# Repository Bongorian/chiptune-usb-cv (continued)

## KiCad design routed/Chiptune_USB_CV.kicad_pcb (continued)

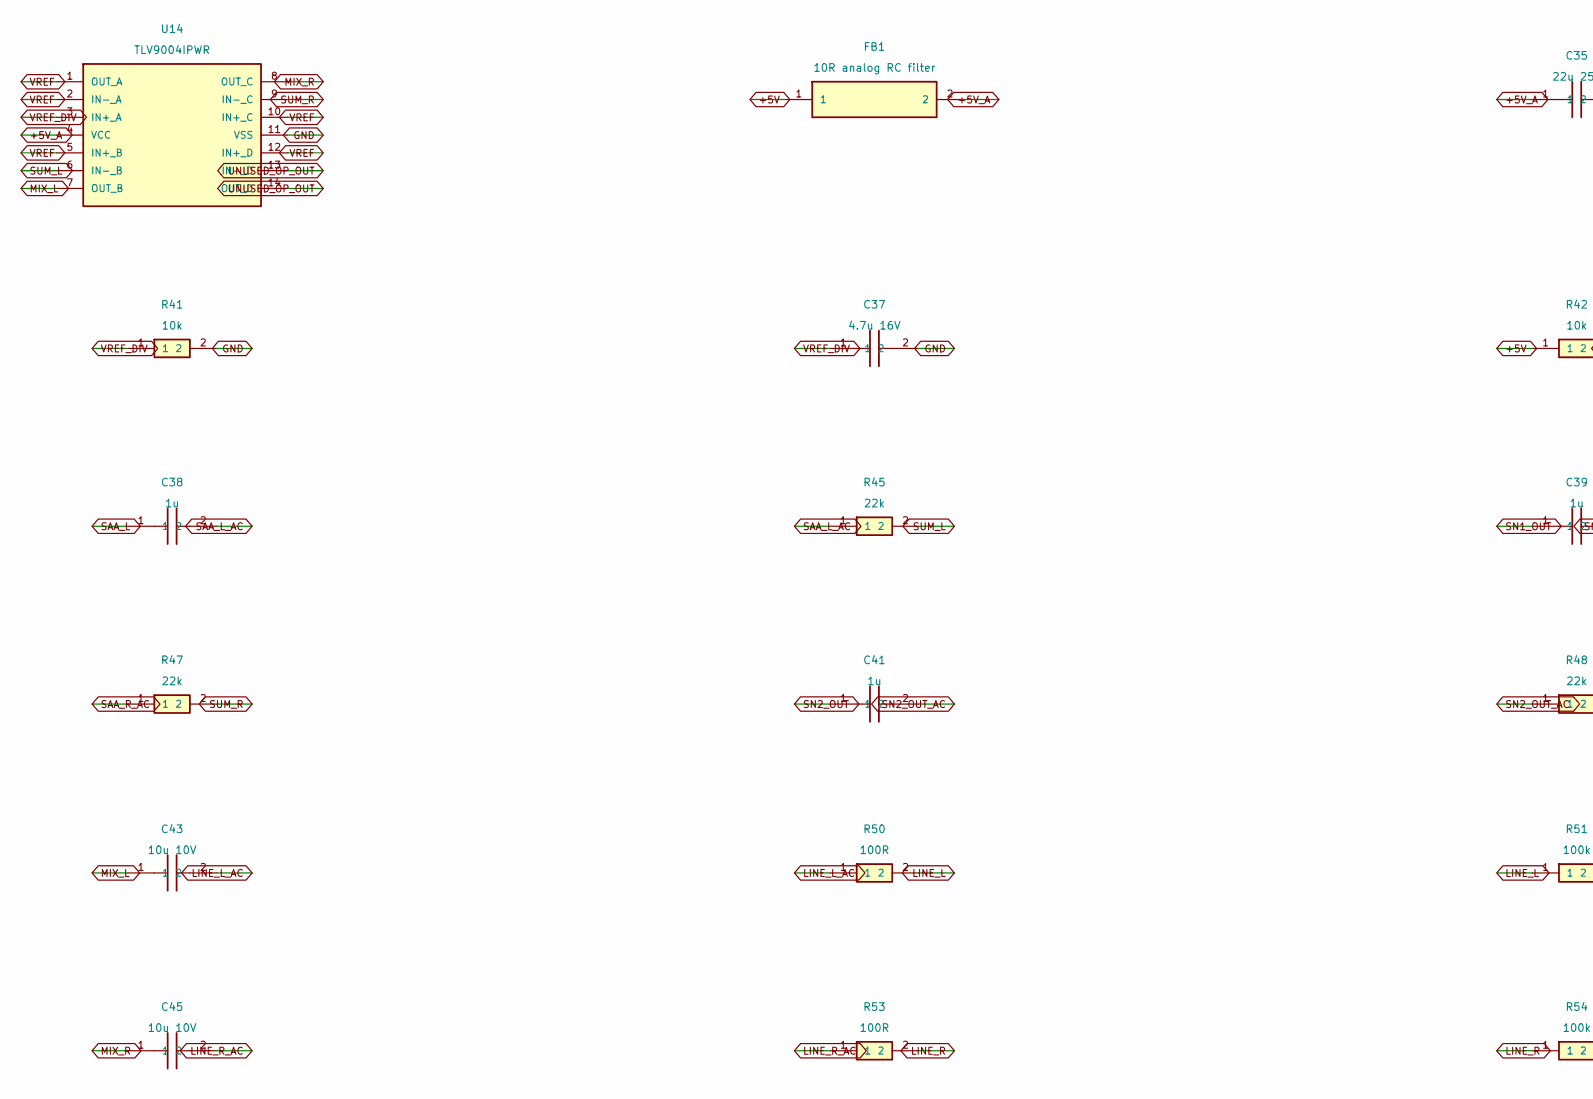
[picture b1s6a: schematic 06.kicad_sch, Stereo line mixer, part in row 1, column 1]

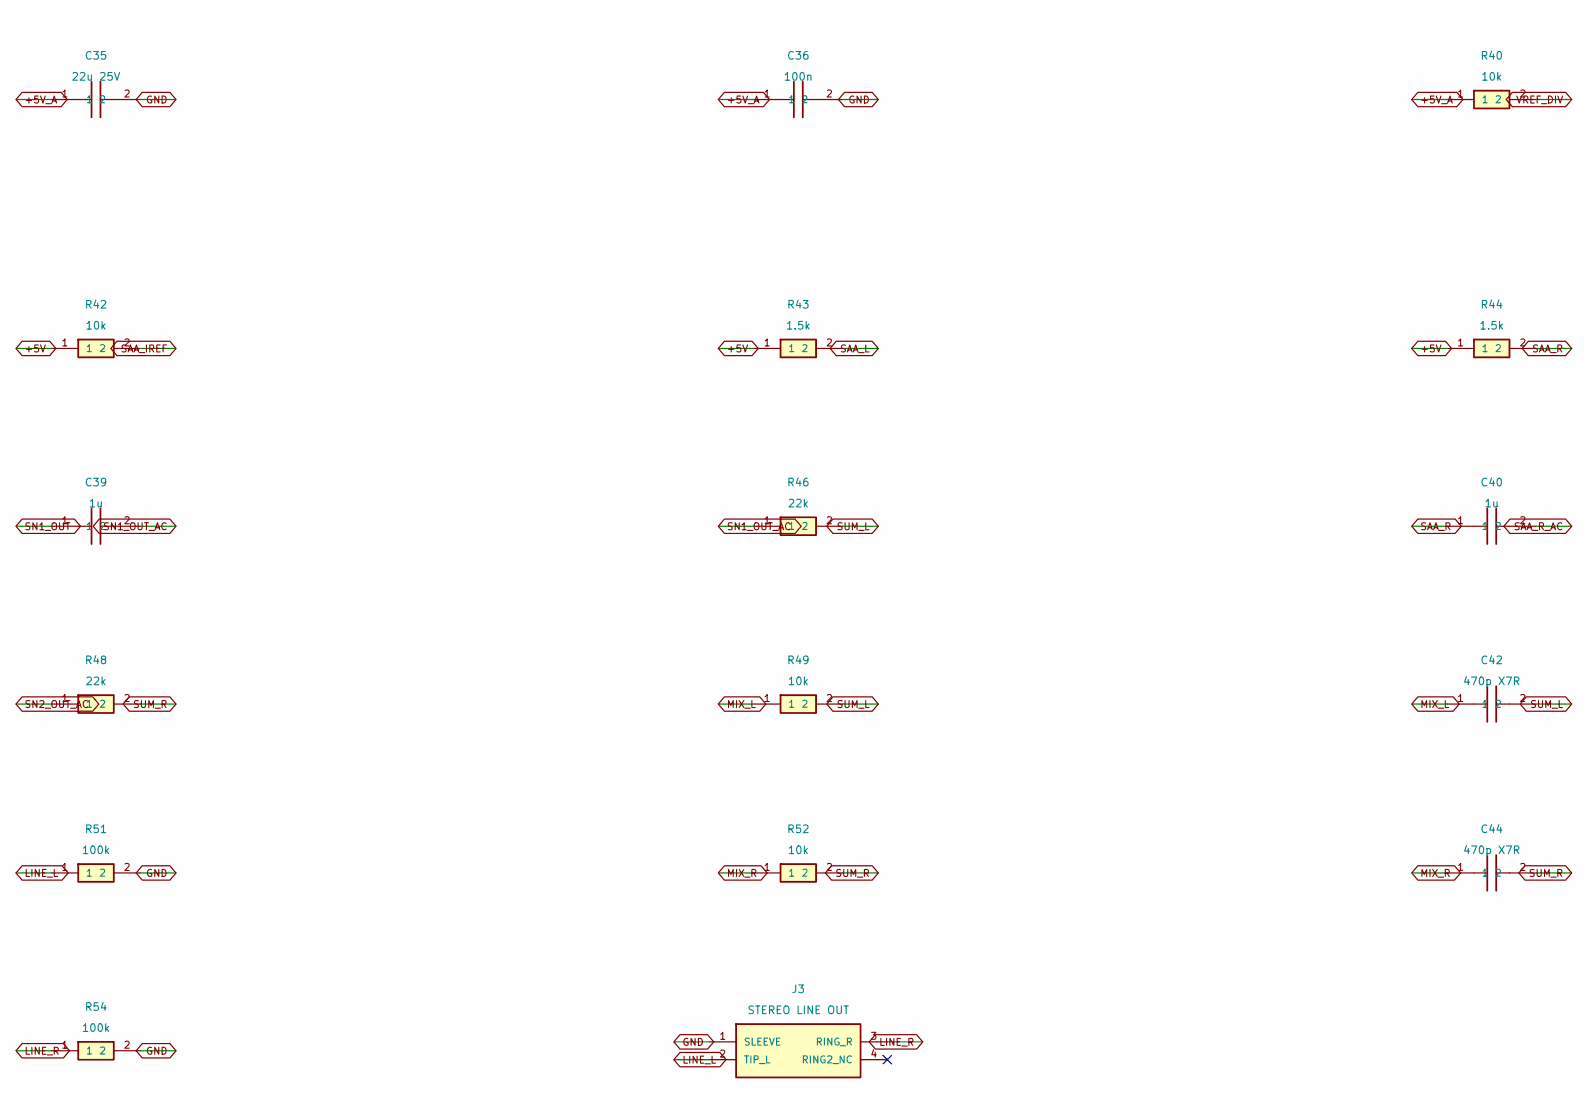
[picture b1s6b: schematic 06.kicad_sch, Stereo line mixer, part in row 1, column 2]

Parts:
C35: 22u 25V; Board_C35; LCSC C45783
C36: 100n; Board_C36; LCSC C14663
C37: 4.7u 16V; Board_C37; LCSC C19666
C38: 1u; Board_C38; LCSC C15849
C39: 1u; Board_C39; LCSC C15849
C40: 1u; Board_C40; LCSC C15849
C41: 1u; Board_C41; LCSC C15849
C42: 470p X7R; Board_C42; LCSC C1620
C43: 10u 10V; Board_C43; LCSC C19702
C44: 470p X7R; Board_C44; LCSC C1620
C45: 10u 10V; Board_C45; LCSC C19702
FB1: 10R analog RC filter; Board_FB1; LCSC C22859
J3: STEREO LINE OUT; Board_J3; LCSC C95562
R40: 10k; Board_R40; LCSC C25804
R41: 10k; Board_R41; LCSC C25804
R42: 10k; Board_R42; LCSC C25804
R43: 1.5k; Board_R43; LCSC C22843
R44: 1.5k; Board_R44; LCSC C22843
R45: 22k; Board_R45; LCSC C31850
R46: 22k; Board_R46; LCSC C31850
R47: 22k; Board_R47; LCSC C31850
R48: 22k; Board_R48; LCSC C31850
R49: 10k; Board_R49; LCSC C25804
R50: 100R; Board_R50; LCSC C22775
R51: 100k; Board_R51; LCSC C25803
R52: 10k; Board_R52; LCSC C25804
R53: 100R; Board_R53; LCSC C22775
R54: 100k; Board_R54; LCSC C25803
U14: TLV9004IPWR; Board_U14; LCSC C2058050

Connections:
+5V: FB1.1, R42.1, R43.1, R44.1; also elsewhere on the board
+5V_A: C35.1, C36.1, FB1.2, R40.1, U14.4 (VCC)
GND: C35.2, C36.2, C37.2, J3.1 (SLEEVE), R41.2, R51.2, R54.2, U14.11 (VSS); also elsewhere on the board
LINE_L: J3.2 (TIP_L), R50.2, R51.1
LINE_L_AC: C43.2, R50.1
LINE_R: J3.3 (RING_R), R53.2, R54.1
LINE_R_AC: C45.2, R53.1
MIX_L: C42.1, C43.1, R49.1, U14.7 (OUT_B)
MIX_R: C44.1, C45.1, R52.1, U14.8 (OUT_C)
SAA_IREF: R42.2; also elsewhere on the board
SAA_L: C38.1, R43.2; also elsewhere on the board
SAA_L_AC: C38.2, R45.1
SAA_R: C40.1, R44.2; also elsewhere on the board
SAA_R_AC: C40.2, R47.1
SN1_OUT: C39.1; also elsewhere on the board
SN1_OUT_AC: C39.2, R46.1
SN2_OUT: C41.1; also elsewhere on the board
SN2_OUT_AC: C41.2, R48.1
SUM_L: C42.2, R45.2, R46.2, R49.2, U14.6 (IN-_B)
SUM_R: C44.2, R47.2, R48.2, R52.2, U14.9 (IN-_C)
UNUSED_OP_OUT: U14.13 (IN-_D), U14.14 (OUT_D)
VREF: U14.1 (OUT_A), U14.2 (IN-_A), U14.5 (IN+_B), U14.10 (IN+_C), U14.12 (IN+_D)
VREF_DIV: C37.1, R40.2, R41.1, U14.3 (IN+_A)

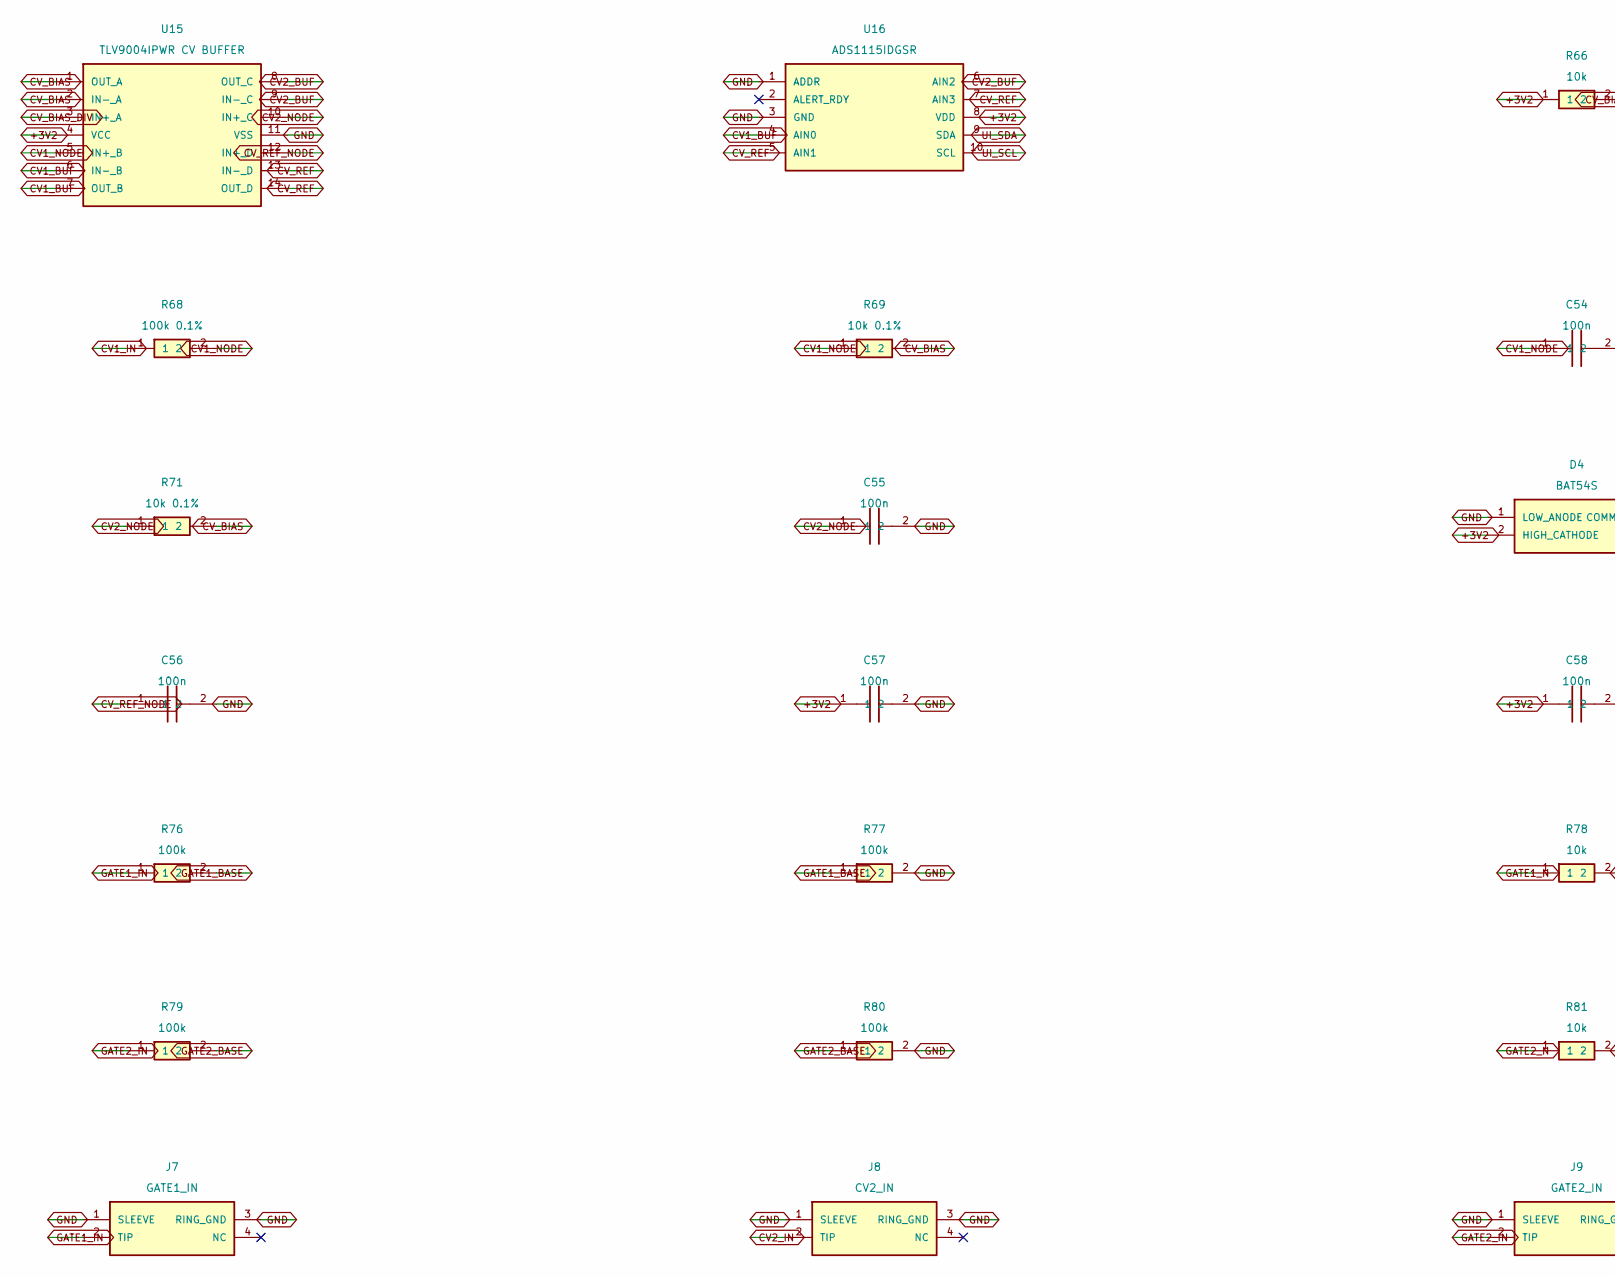
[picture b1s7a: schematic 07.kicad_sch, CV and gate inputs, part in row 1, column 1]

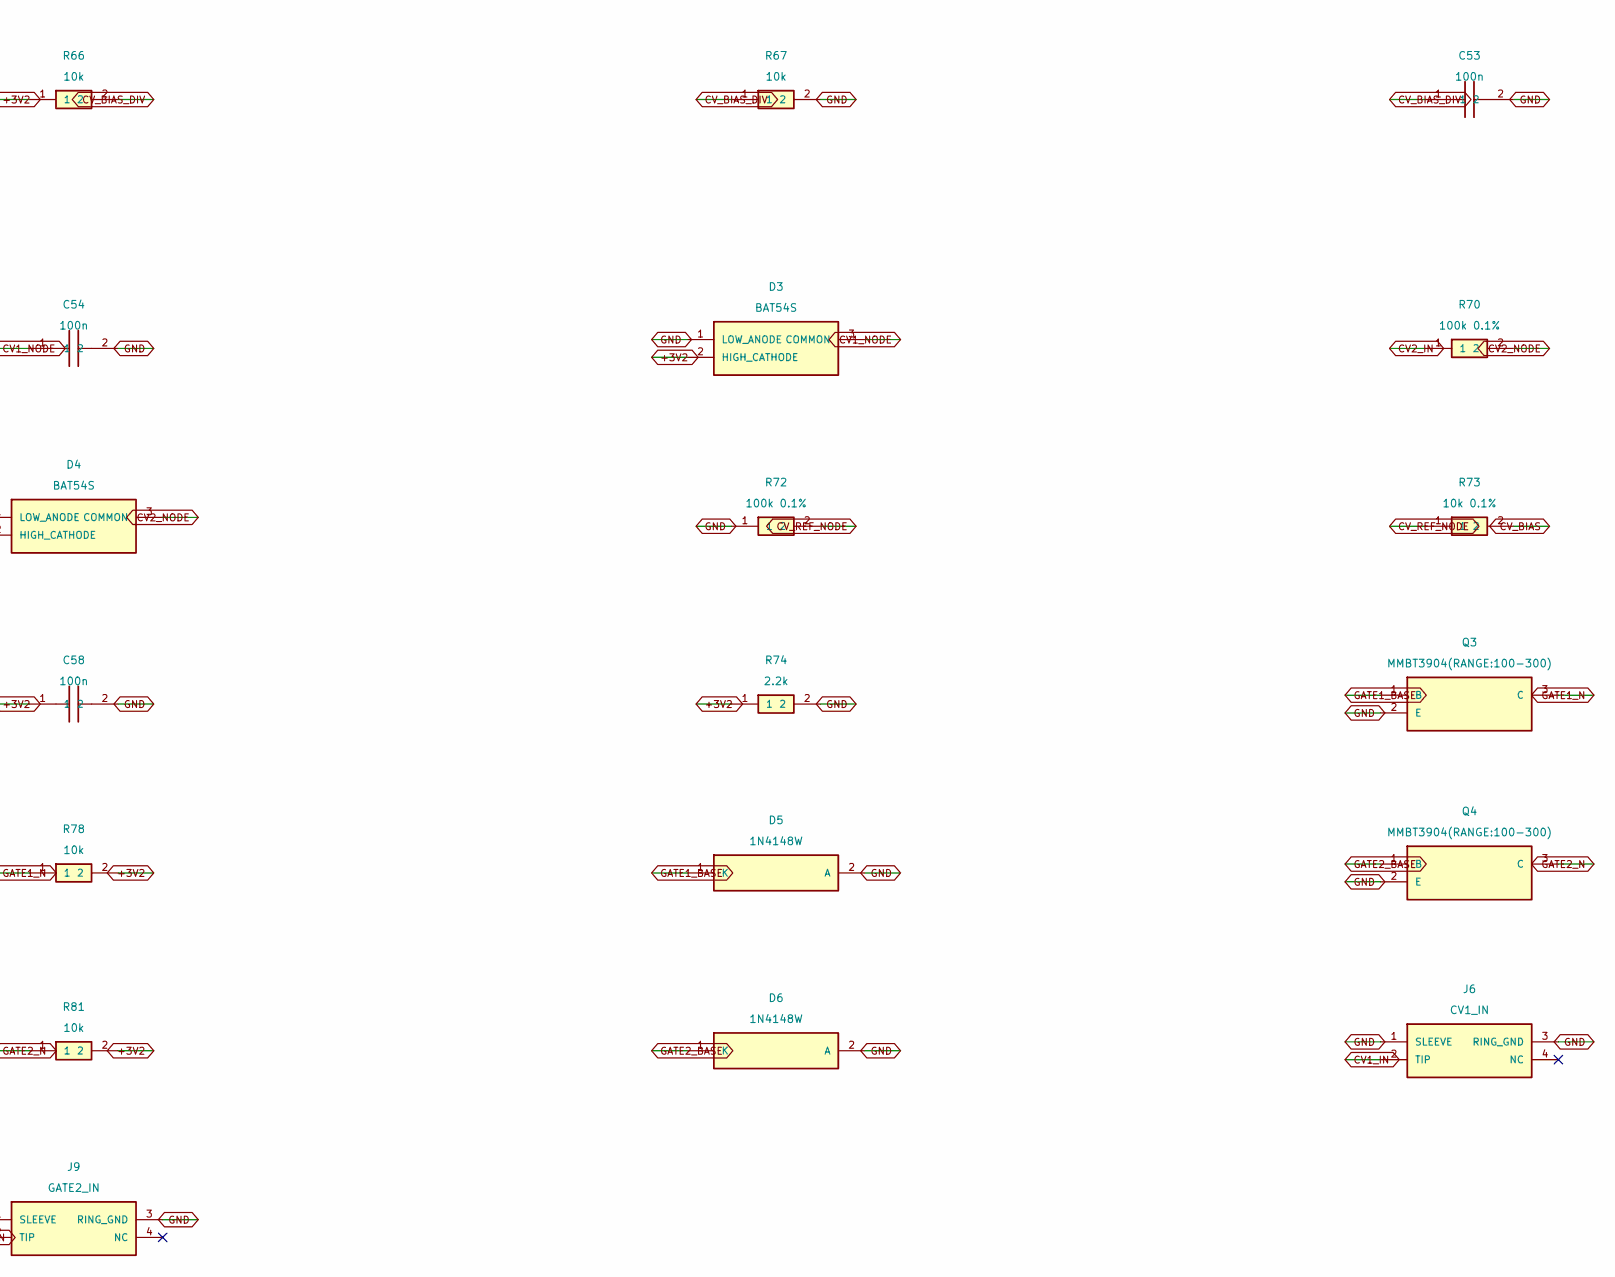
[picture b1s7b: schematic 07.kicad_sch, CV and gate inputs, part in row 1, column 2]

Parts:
C53: 100n; Board_C53; LCSC C14663
C54: 100n; Board_C54; LCSC C14663
C55: 100n; Board_C55; LCSC C14663
C56: 100n; Board_C56; LCSC C14663
C57: 100n; Board_C57; LCSC C14663
C58: 100n; Board_C58; LCSC C14663
D3: BAT54S; Board_D3; LCSC C83935
D4: BAT54S; Board_D4; LCSC C83935
D5: 1N4148W; Board_D5; LCSC C81598
D6: 1N4148W; Board_D6; LCSC C81598
J6: CV1_IN; Board_J6; LCSC C95562
J7: GATE1_IN; Board_J7; LCSC C95562
J8: CV2_IN; Board_J8; LCSC C95562
J9: GATE2_IN; Board_J9; LCSC C95562
Q3: MMBT3904(RANGE:100-300); Board_Q3; LCSC C20526
Q4: MMBT3904(RANGE:100-300); Board_Q4; LCSC C20526
R66: 10k; Board_R66; LCSC C25804
R67: 10k; Board_R67; LCSC C25804
R68: 100k 0.1%; Board_R68; LCSC C855559
R69: 10k 0.1%; Board_R69; LCSC C95204
R70: 100k 0.1%; Board_R70; LCSC C855559
R71: 10k 0.1%; Board_R71; LCSC C95204
R72: 100k 0.1%; Board_R72; LCSC C855559
R73: 10k 0.1%; Board_R73; LCSC C95204
R74: 2.2k; Board_R74; LCSC C4190
R76: 100k; Board_R76; LCSC C25803
R77: 100k; Board_R77; LCSC C25803
R78: 10k; Board_R78; LCSC C25804
R79: 100k; Board_R79; LCSC C25803
R80: 100k; Board_R80; LCSC C25803
R81: 10k; Board_R81; LCSC C25804
U15: TLV9004IPWR CV BUFFER; Board_U15; LCSC C2058050
U16: ADS1115IDGSR; Board_U16; LCSC C37593

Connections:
+3V2: C57.1, C58.1, D3.2 (HIGH_CATHODE), D4.2 (HIGH_CATHODE), R66.1, R74.1, R78.2, R81.2, U15.4 (VCC), U16.8 (VDD); also elsewhere on the board
CV1_BUF: U15.6 (IN-_B), U15.7 (OUT_B), U16.4 (AIN0)
CV1_IN: J6.2 (TIP), R68.1
CV1_NODE: C54.1, D3.3 (COMMON), R68.2, R69.1, U15.5 (IN+_B)
CV2_BUF: U15.8 (OUT_C), U15.9 (IN-_C), U16.6 (AIN2)
CV2_IN: J8.2 (TIP), R70.1
CV2_NODE: C55.1, D4.3 (COMMON), R70.2, R71.1, U15.10 (IN+_C)
CV_BIAS: R69.2, R71.2, R73.2, U15.1 (OUT_A), U15.2 (IN-_A)
CV_BIAS_DIV: C53.1, R66.2, R67.1, U15.3 (IN+_A)
CV_REF: U15.13 (IN-_D), U15.14 (OUT_D), U16.5 (AIN1), U16.7 (AIN3)
CV_REF_NODE: C56.1, R72.2, R73.1, U15.12 (IN+_D)
GATE1_BASE: D5.1 (K), Q3.1 (B), R76.2, R77.1
GATE1_IN: J7.2 (TIP), R76.1
GATE1_N: Q3.3 (C), R78.1; also elsewhere on the board
GATE2_BASE: D6.1 (K), Q4.1 (B), R79.2, R80.1
GATE2_IN: J9.2 (TIP), R79.1
GATE2_N: Q4.3 (C), R81.1; also elsewhere on the board
GND: C53.2, C54.2, C55.2, C56.2, C57.2, C58.2, D3.1 (LOW_ANODE), D4.1 (LOW_ANODE), D5.2 (A), D6.2 (A), J6.1 (SLEEVE), J6.3 (RING_GND), J7.1 (SLEEVE), J7.3 (RING_GND), J8.1 (SLEEVE), J8.3 (RING_GND), J9.1 (SLEEVE), J9.3 (RING_GND), Q3.2 (E), Q4.2 (E), R67.2, R72.1, R74.2, R77.2, R80.2, U15.11 (VSS), U16.1 (ADDR), U16.3 (GND); also elsewhere on the board
UI_SCL: U16.10 (SCL); also elsewhere on the board
UI_SDA: U16.9 (SDA); also elsewhere on the board

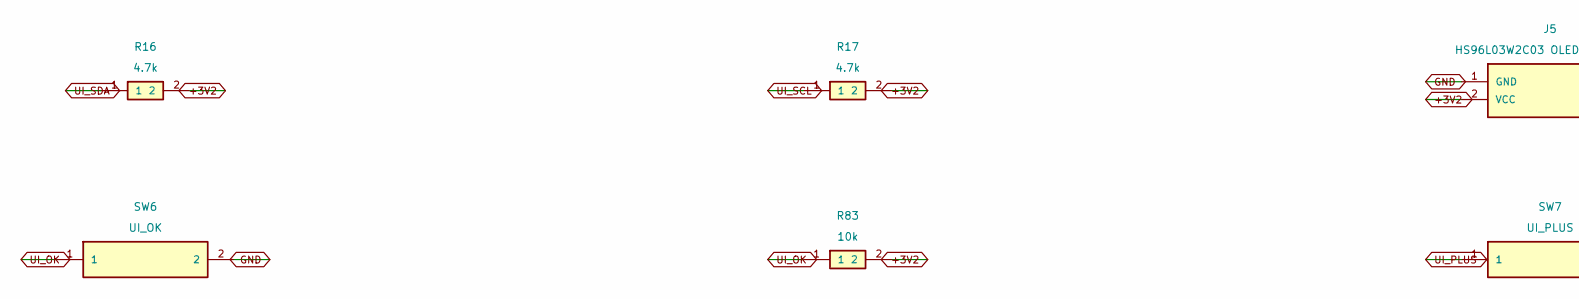
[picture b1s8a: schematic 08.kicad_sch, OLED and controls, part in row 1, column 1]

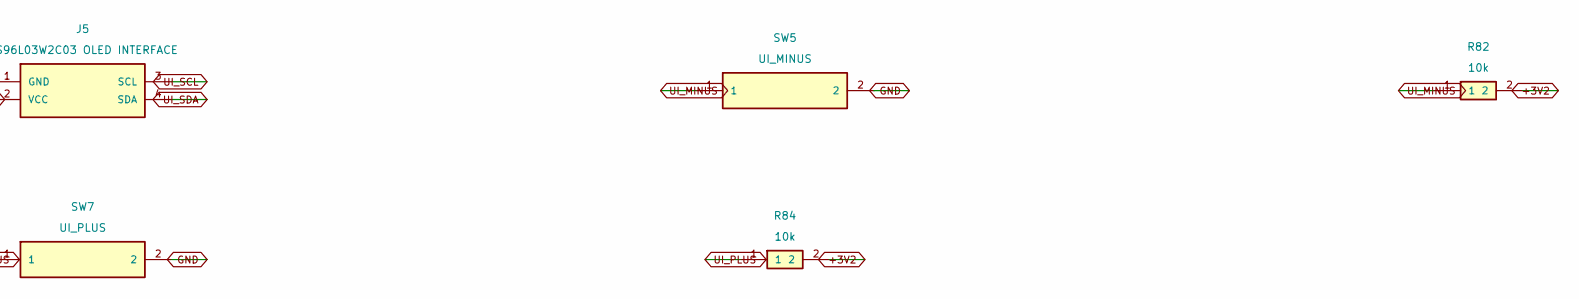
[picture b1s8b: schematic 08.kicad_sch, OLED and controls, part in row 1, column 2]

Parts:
J5: HS96L03W2C03 OLED INTERFACE; Board_J5; LCSC C5248080
R16: 4.7k; Board_R16; LCSC C23162
R17: 4.7k; Board_R17; LCSC C23162
R82: 10k; Board_R82; LCSC C25804
R83: 10k; Board_R83; LCSC C25804
R84: 10k; Board_R84; LCSC C25804
SW5: UI_MINUS; Board_SW5; LCSC C318884
SW6: UI_OK; Board_SW6; LCSC C318884
SW7: UI_PLUS; Board_SW7; LCSC C318884

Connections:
+3V2: J5.2 (VCC), R16.2, R17.2, R82.2, R83.2, R84.2; also elsewhere on the board
GND: J5.1 (GND), SW5.2, SW6.2, SW7.2; also elsewhere on the board
UI_MINUS: R82.1, SW5.1; also elsewhere on the board
UI_OK: R83.1, SW6.1; also elsewhere on the board
UI_PLUS: R84.1, SW7.1; also elsewhere on the board
UI_SCL: J5.3 (SCL), R17.1; also elsewhere on the board
UI_SDA: J5.4 (SDA), R16.1; also elsewhere on the board

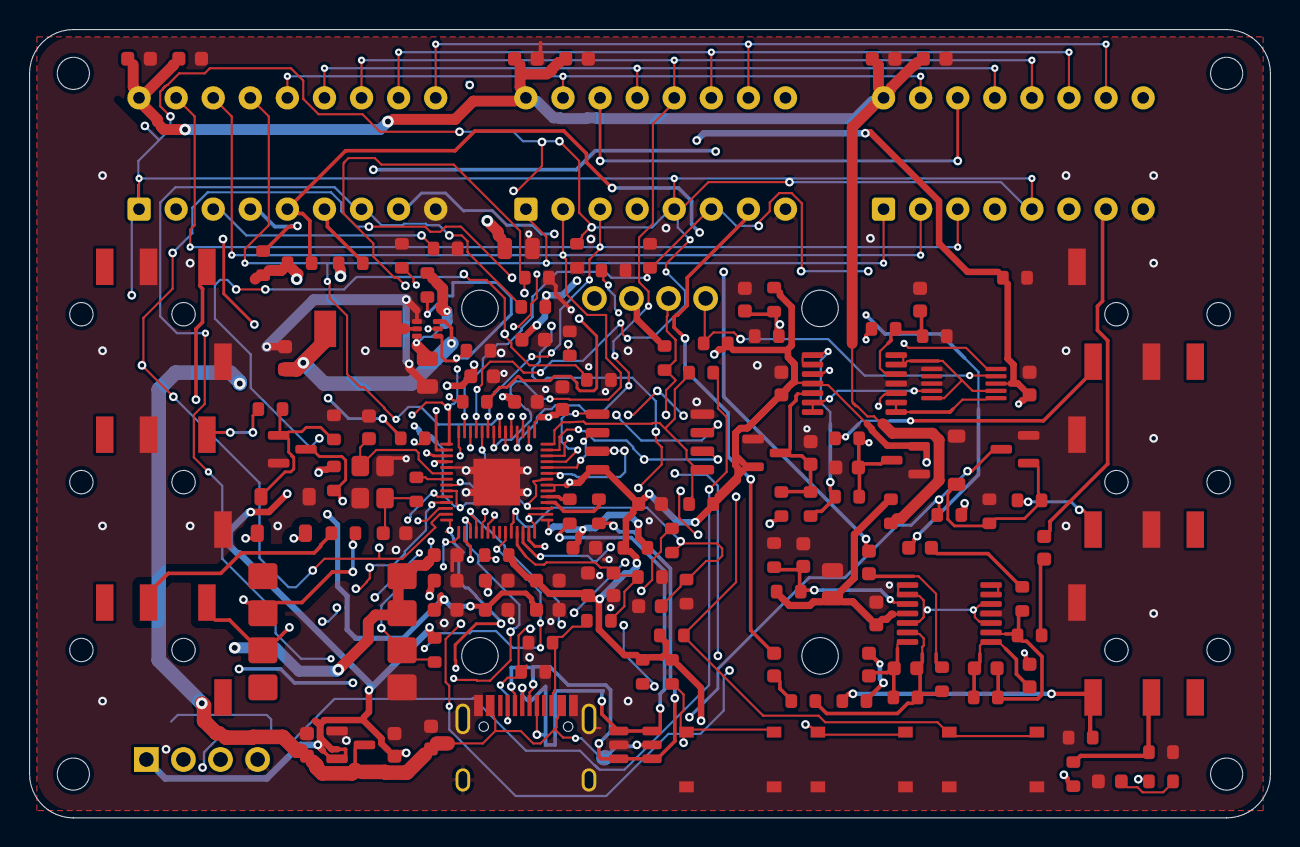
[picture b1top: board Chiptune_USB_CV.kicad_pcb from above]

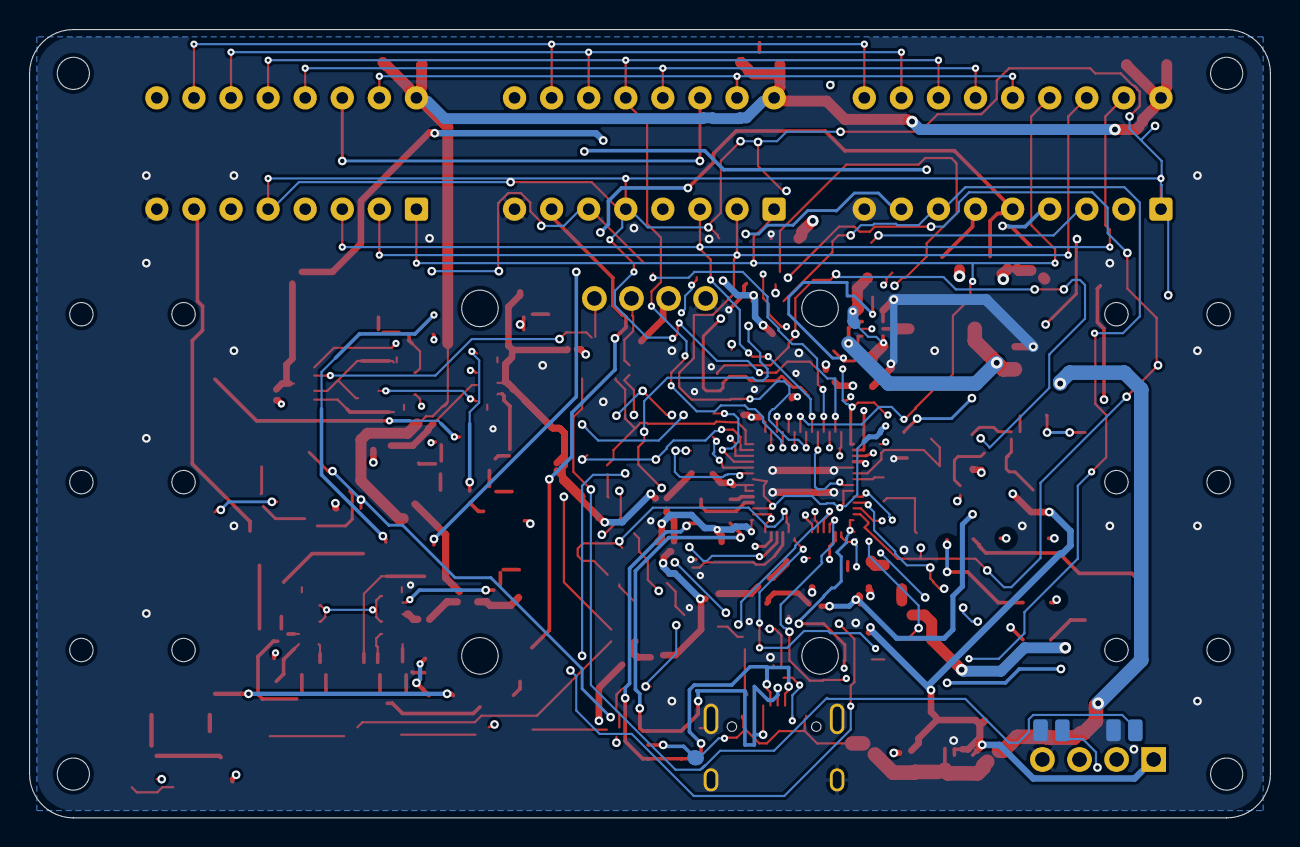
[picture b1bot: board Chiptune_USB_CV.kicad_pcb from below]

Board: 4 copper layers, 85.0 x 54.0 mm, 152 parts (2 on the bottom side), 96 nets.

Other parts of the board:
H1: MountingHole_2.2mm_M2; Board_H1
H2: MountingHole_2.2mm_M2; Board_H2
H3: MountingHole_2.2mm_M2; Board_H3
H4: MountingHole_2.2mm_M2; Board_H4

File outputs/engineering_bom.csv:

Reference,Value,Footprint,LCSC,Side,Notes
U1,RP2040,Chiptune:Board_U1,C2040,F,
U2,W25Q16JVSSIQ,Chiptune:Board_U2,C131025,F,
Y1,ABM8-272-T3 12MHz,Chiptune:Board_Y1,C20625731,F,
R1,1k,Chiptune:Board_R1,C21190,F,
C1,15p C0G,Chiptune:Board_C1,C1644,F,
C2,15p C0G,Chiptune:Board_C2,C1644,F,
R2,10k,Chiptune:Board_R2,C25804,F,
R3,10k,Chiptune:Board_R3,C25804,F,
C3,100n,Chiptune:Board_C3,C14663,F,
C4,100n,Chiptune:Board_C4,C14663,F,
C5,100n,Chiptune:Board_C5,C14663,F,
C6,100n,Chiptune:Board_C6,C14663,F,
C7,100n,Chiptune:Board_C7,C14663,F,
C8,100n,Chiptune:Board_C8,C14663,F,
C9,100n,Chiptune:Board_C9,C14663,F,
C10,100n,Chiptune:Board_C10,C14663,F,
C11,100n,Chiptune:Board_C11,C14663,F,
C12,100n,Chiptune:Board_C12,C14663,F,
C13,100n,Chiptune:Board_C13,C14663,F,
C14,1u,Chiptune:Board_C14,C15849,F,
C15,1u,Chiptune:Board_C15,C15849,F,
R4,10R,Chiptune:Board_R4,C22859,F,
R5,1k,Chiptune:Board_R5,C21190,F,
J4,SWD,Chiptune:Board_J4,,F,"Hand solder, optional"
U3,TPS61023DRLR,Chiptune:Board_U3,C919459,F,
R6,100k,Chiptune:Board_R6,C25803,F,
L1,SLO0520H1R0MTT 1uH,Chiptune:Board_L1,C325980,F,"1uH; Isat 8A typ, Irms 5A typ; manufacturer drawing verified"
C16,1u,Chiptune:Board_C16,C15849,F,
C18,22u 25V,Chiptune:Board_C18,C45783,F,
C19,22u 25V,Chiptune:Board_C19,C45783,F,
R7,22k,Chiptune:Board_R7,C31850,F,
R8,3k,Chiptune:Board_R8,C4211,F,
U5,AP2120N-3.2TRG1,Chiptune:Board_U5,C6500828,F,3.2V +/-2%; OLED maximum 3.3V
C21,4.7u 16V,Chiptune:Board_C21,C19666,F,
C22,4.7u 16V,Chiptune:Board_C22,C19666,F,
J1,USB-C MIDI DEVICE / POWER,Chiptune:Board_J1,C165948,F,
U9,USBLC6-2SC6,Chiptune:Board_U9,C7519,F,
R11,27R,Chiptune:Board_R11,C25190,F,
R12,27R,Chiptune:Board_R12,C25190,F,
R16,4.7k,Chiptune:Board_R16,C23162,F,
R17,4.7k,Chiptune:Board_R17,C23162,F,
U10,SAA1099 DIP18,Chiptune:Board_U10,,F,User supplied IC; hand solder DIP18 socket; GPIO0..7 word equals logical byte; reverse8 only for individual PIN_Dn writes
U11,SN76489AN DIP16,Chiptune:Board_U11,,F,"User supplied IC; hand solder DIP16 socket; READY unused, firmware write wait >=10us at 4MHz"
U12,SN76489AN DIP16,Chiptune:Board_U12,,F,"User supplied IC; hand solder DIP16 socket; READY unused, firmware write wait >=10us at 4MHz"
R26,33R,Chiptune:Board_R26,C23140,F,
R27,33R,Chiptune:Board_R27,C23140,F,
R28,100k,Chiptune:Board_R28,C25803,F,
R29,100k,Chiptune:Board_R29,C25803,F,
R30,100k,Chiptune:Board_R30,C25803,F,
R31,100k,Chiptune:Board_R31,C25803,F,
R32,10k,Chiptune:Board_R32,C25804,F,
R35,100k,Chiptune:Board_R35,C25803,F,
R36,100k,Chiptune:Board_R36,C25803,F,
R37,100k,Chiptune:Board_R37,C25803,F,
C28,100n,Chiptune:Board_C28,C14663,F,
C29,100n,Chiptune:Board_C29,C14663,F,
C30,100n,Chiptune:Board_C30,C14663,F,
C31,4.7u 16V,Chiptune:Board_C31,C19666,F,
C32,4.7u 16V,Chiptune:Board_C32,C19666,F,
C33,4.7u 16V,Chiptune:Board_C33,C19666,F,
J2,TRS MIDI IN TYPE A,Chiptune:Board_J2,C95562,F,
R38,220R,Chiptune:Board_R38,C22962,F,
D1,1N4148W,Chiptune:Board_D1,C81598,F,
U13,6N137S(T1),Chiptune:Board_U13,C191867,F,
R39,2.2k,Chiptune:Board_R39,C4190,F,
C34,100n,Chiptune:Board_C34,C14663,F,
U14,TLV9004IPWR,Chiptune:Board_U14,C2058050,F,
FB1,10R analog RC filter,Chiptune:Board_FB1,C22859,F,
C35,22u 25V,Chiptune:Board_C35,C45783,F,
C36,100n,Chiptune:Board_C36,C14663,F,
R40,10k,Chiptune:Board_R40,C25804,F,
R41,10k,Chiptune:Board_R41,C25804,F,
C37,4.7u 16V,Chiptune:Board_C37,C19666,F,
R42,10k,Chiptune:Board_R42,C25804,F,
R43,1.5k,Chiptune:Board_R43,C22843,F,
R44,1.5k,Chiptune:Board_R44,C22843,F,
C38,1u,Chiptune:Board_C38,C15849,F,
R45,22k,Chiptune:Board_R45,C31850,F,
C39,1u,Chiptune:Board_C39,C15849,F,
R46,22k,Chiptune:Board_R46,C31850,F,
C40,1u,Chiptune:Board_C40,C15849,F,
R47,22k,Chiptune:Board_R47,C31850,F,
C41,1u,Chiptune:Board_C41,C15849,F,
R48,22k,Chiptune:Board_R48,C31850,F,
R49,10k,Chiptune:Board_R49,C25804,F,
C42,470p X7R,Chiptune:Board_C42,C1620,F,
C43,10u 10V,Chiptune:Board_C43,C19702,F,
R50,100R,Chiptune:Board_R50,C22775,F,
R51,100k,Chiptune:Board_R51,C25803,F,
R52,10k,Chiptune:Board_R52,C25804,F,
C44,470p X7R,Chiptune:Board_C44,C1620,F,
C45,10u 10V,Chiptune:Board_C45,C19702,F,
R53,100R,Chiptune:Board_R53,C22775,F,
R54,100k,Chiptune:Board_R54,C25803,F,
J3,STEREO LINE OUT,Chiptune:Board_J3,C95562,F,
D2,RED STATUS,Chiptune:Board_D2,C2286,F,Basic red status LED; same 0603 K/A footprint; R55 2.2k unchanged; selected for cost.
R55,2.2k,Chiptune:Board_R55,C4190,F,
R58,5.1k,Chiptune:Board_R58,C23186,F,
R61,100k,Chiptune:Board_R61,C25803,F,
R62,100k,Chiptune:Board_R62,C25803,F,
C50,100n,Chiptune:Board_C50,C14663,F,
R59,5.1k,Chiptune:Board_R59,C23186,F,
R63,100k,Chiptune:Board_R63,C25803,F,
R64,100k,Chiptune:Board_R64,C25803,F,
C51,100n,Chiptune:Board_C51,C14663,F,
C52,1u,Chiptune:Board_C52,C15849,F,
U15,TLV9004IPWR CV BUFFER,Chiptune:Board_U15,C2058050,F,
U16,ADS1115IDGSR,Chiptune:Board_U16,C37593,F,
R66,10k,Chiptune:Board_R66,C25804,F,
R67,10k,Chiptune:Board_R67,C25804,F,
C53,100n,Chiptune:Board_C53,C14663,F,
R68,100k 0.1%,Chiptune:Board_R68,C855559,F,
R69,10k 0.1%,Chiptune:Board_R69,C95204,F,
C54,100n,Chiptune:Board_C54,C14663,F,
D3,BAT54S,Chiptune:Board_D3,C83935,F,
R70,100k 0.1%,Chiptune:Board_R70,C855559,F,
R71,10k 0.1%,Chiptune:Board_R71,C95204,F,
C55,100n,Chiptune:Board_C55,C14663,F,
D4,BAT54S,Chiptune:Board_D4,C83935,F,
R72,100k 0.1%,Chiptune:Board_R72,C855559,F,
R73,10k 0.1%,Chiptune:Board_R73,C95204,F,
C56,100n,Chiptune:Board_C56,C14663,F,
C57,100n,Chiptune:Board_C57,C14663,F,
C58,100n,Chiptune:Board_C58,C14663,F,
R74,2.2k,Chiptune:Board_R74,C4190,F,
Q3,MMBT3904(RANGE:100-300),Chiptune:Board_Q3,C20526,F,Basic substitution; SOT-23 pin 1 B / 2 E / 3 C; same footprint and wiring.
R76,100k,Chiptune:Board_R76,C25803,F,
R77,100k,Chiptune:Board_R77,C25803,F,
R78,10k,Chiptune:Board_R78,C25804,F,
D5,1N4148W,Chiptune:Board_D5,C81598,F,
Q4,MMBT3904(RANGE:100-300),Chiptune:Board_Q4,C20526,F,Basic substitution; SOT-23 pin 1 B / 2 E / 3 C; same footprint and wiring.
R79,100k,Chiptune:Board_R79,C25803,F,
R80,100k,Chiptune:Board_R80,C25803,F,
R81,10k,Chiptune:Board_R81,C25804,F,
D6,1N4148W,Chiptune:Board_D6,C81598,F,
J6,CV1_IN,Chiptune:Board_J6,C95562,F,
J7,GATE1_IN,Chiptune:Board_J7,C95562,F,
J8,CV2_IN,Chiptune:Board_J8,C95562,F,
J9,GATE2_IN,Chiptune:Board_J9,C95562,F,
J5,HS96L03W2C03 OLED INTERFACE,Chiptune:Board_J5,C5248080,F,"Manual assembly; 27.3x27.8mm SSD1315 module on 5mm M2 spacers, not SMT placed"
SW5,UI_MINUS,Chiptune:Board_SW5,C318884,F,
R82,10k,Chiptune:Board_R82,C25804,F,
SW6,UI_OK,Chiptune:Board_SW6,C318884,F,
R83,10k,Chiptune:Board_R83,C25804,F,
SW7,UI_PLUS,Chiptune:Board_SW7,C318884,F,
R84,10k,Chiptune:Board_R84,C25804,F,
JP1,BOOT,Chiptune:Board_JP1,,B,Rear service pads; short briefly for BOOT/RESET
JP2,RESET,Chiptune:Board_JP2,,B,Rear service pads; short briefly for BOOT/RESET

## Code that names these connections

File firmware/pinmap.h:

#pragma once
// Generated from scripts/design.py; RP2040 GPIO assignments
#define PIN_D7 0
#define PIN_D6 1
#define PIN_D5 2
#define PIN_D4 3
#define PIN_D3 4
#define PIN_D2 5
#define PIN_D1 6
#define PIN_D0 7
#define PIN_WR_N 8
#define PIN_SAA_CS_N 9
#define PIN_SN1_CS_N 10
#define PIN_SN2_CS_N 11
#define PIN_SAA_A0 12
#define PIN_MIDI_RX 13
#define PIN_SAA_CLK_RAW 14
#define PIN_GATE1_N 15
#define PIN_SN_CLK_RAW 16
#define PIN_GATE2_N 17
#define PIN_UI_SDA 18
#define PIN_UI_SCL 19
#define PIN_UI_MINUS 20
#define PIN_UI_OK 21
#define PIN_UI_PLUS 22
#define PIN_SAA_DTACK_N 25
#define PIN_CC1_ADC 26
#define PIN_CC2_ADC 27
#define PIN_STATUS_LED 28
#define PIN_SOUND_ENABLE 29

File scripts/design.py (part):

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# Group 1: MCU, flash, oscillator, programming.
rptext=Path('/usr/share/kicad/symbols/MCU_RaspberryPi.kicad_sym').read_text().split('\n\t(symbol "RP2350')[0]
rppins=[(n,name,typ) for typ,name,n in re.findall(r'\(pin (\w+) \w+.*?\(name "([^"]*)".*?\(number "([^"]*)"',rptext,re.S)]
gpio={**{i:f'D{i}' for i in range(8)},8:'WR_N',9:'SAA_CS_N',10:'SN1_CS_N',11:'SN2_CS_N',12:'SAA_A0',
      13:'MIDI_RX',14:'SAA_CLK_RAW',15:'TYPEC_ID_N',16:'SN_CLK_RAW',17:'HOST_DISABLE',18:'CC_SDA',19:'CC_SCL',
      20:'CC_EN_N',21:'USB_FAULT_N',22:'MODE_BUTTON',23:'SN1_READY',24:'SN2_READY',25:'SAA_DTACK_N',
      26:'RAIL_ADC',27:'VBUS_PRESENT_N',28:'STATUS_LED',29:None}
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add('U1','RP2040','Package_DFN_QFN:QFN-56-1EP_7x7mm_P0.4mm_EP3.2x3.2mm',rn,1,25,17,0,'C2040',rppins)
add('U2','W25Q16JVSSIQ','Package_SO:SOIC-8_5.3x5.3mm_P1.27mm',{1:'FLASH_CS',2:'FLASH_D1',3:'FLASH_D2',4:'GND',5:'FLASH_D0',6:'FLASH_CLK',7:'FLASH_D3',8:'+3V3'},1,15,17,90,'C131025',
    [('1','CS_N','input'),('2','IO1','bidirectional'),('3','IO2','bidirectional'),('4','GND','power_in'),('5','IO0','bidirectional'),('6','CLK','input'),('7','IO3','bidirectional'),('8','VCC','power_in')])
add('Y1','ABM8-272-T3 12MHz','Crystal:Crystal_SMD_3225-4Pin_3.2x2.5mm',{1:'XIN',2:'GND',3:'XTAL_OUT',4:'GND'},1,25,26,0,'C20625731',[(str(i),nm,'passive') for i,nm in enumerate(['XIN','CASE','XOUT','CASE'],1)])
r('1k','XOUT','XTAL_OUT',1,28.5,26,90,c='C21190')
c('15p C0G','XIN','GND',1,22,27,90,code='C1644'); c('15p C0G','XTAL_OUT','GND',1,28.5,29,90,code='C1644')
r('10k','FLASH_CS','+3V3',1,12,12,c='C25804'); r('10k','RUN','+3V3',1,35,17,90,c='C25804')
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r('10k','MODE_BUTTON','+3V3',3,38,20,90,c='C25804')

# Group 4: real sound chips, common data bus, independent selects.
saapins=[('1','WR_N','input'),('2','CS_N','input'),('3','A0','input'),('4','OUT_R','output'),('5','OUT_L','output'),('6','IREF','passive'),('7','DTACK_N','open_collector'),('8','CLK','input'),('9','VSS','power_in')]+[(str(10+i),f'D{i}','input') for i in range(8)]+[('18','VDD','power_in')]
snmap={1:'D2',2:'D1',3:'D0',4:'READY',5:'WE_N',6:'CE_N',7:'AUDIO',8:'GND',9:'NC',10:'D7',11:'D6',12:'D5',13:'D4',14:'CLK',15:'D3',16:'VCC'}
saan={1:'WR_N',2:'SAA_CS_N',3:'SAA_A0',4:'SAA_R',5:'SAA_L',6:'SAA_IREF',7:'SAA_DTACK_N',8:'SAA_CLK',9:'GND',18:'+5V',**{10+i:f'D{i}' for i in range(8)}}
add('U10','SAA1099 DIP18','Package_DIP:DIP-18_W7.62mm_Socket',saan,4,51,7,0,'',saapins,notes='User supplied IC; hand solder DIP18 socket')
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for x,y in [(61,11),(74,11),(47,18)]: c('4.7u 16V','+5V','GND',4,x,y,90,code='C19666')

# Group 5: isolated TRS Type A MIDI input. Sleeve and jack switch are not grounded.
add('J2','TRS MIDI IN TYPE A','Chiptune:PJ320D4A',{1:None,2:'MIDI_TIP',3:'MIDI_RING',4:None},5,76.7,34.5,180,'C95562', [('1','SLEEVE_ISOLATED','passive'),('2','TIP','passive'),('3','RING','passive'),('4','RING2_NC','passive')])
r('220R','MIDI_RING','MIDI_ANODE',5,65,35,c='C22962')
add('D1','1N4148W','Diode_SMD:D_SOD-123',{1:'MIDI_ANODE',2:'MIDI_TIP'},5,65,39,0,'C81598',[('1','K','passive'),('2','A','passive')])
add('U13','6N137S(T1)','Package_DIP:SMDIP-8_W9.53mm',{1:None,2:'MIDI_ANODE',3:'MIDI_TIP',4:None,5:'GND',6:'MIDI_RX',7:'+5V',8:'+5V'},5,56,38,0,'C191867',
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    r('10k','MIX_'+ch,'SUM_'+ch,6,x,y,c='C25804'); c('470p X7R','MIX_'+ch,'SUM_'+ch,6,x+3,y,code='C1620')
    c('10u 10V','MIX_'+ch,'LINE_'+ch+'_AC',6,64,y,90,code='C19702')
    r('100R','LINE_'+ch+'_AC','LINE_'+ch,6,68,y,90,c='C22775'); r('100k','LINE_'+ch,'GND',6,71,y,90,c='C25803')
add('J3','STEREO LINE OUT','Chiptune:PJ320D4A',{1:'GND',2:'LINE_L',3:'LINE_R',4:None},6,76.7,44.5,180,'C95562',[('1','SLEEVE','passive'),('2','TIP_L','passive'),('3','RING_R','passive'),('4','RING2_NC','passive')])
# Status and spare ADC: GPIO26 senses 5V health in this revision, not raw battery.
rn['38']='RAIL_ADC'
add('D2','GREEN STATUS','LED_SMD:LED_0603_1608Metric',{1:'GND',2:'LED_A'},1,35,29,0,'C72043',[('1','K','passive'),('2','A','passive')])
r('2.2k','STATUS_LED','LED_A',1,35,32,90,c='C4190')
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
